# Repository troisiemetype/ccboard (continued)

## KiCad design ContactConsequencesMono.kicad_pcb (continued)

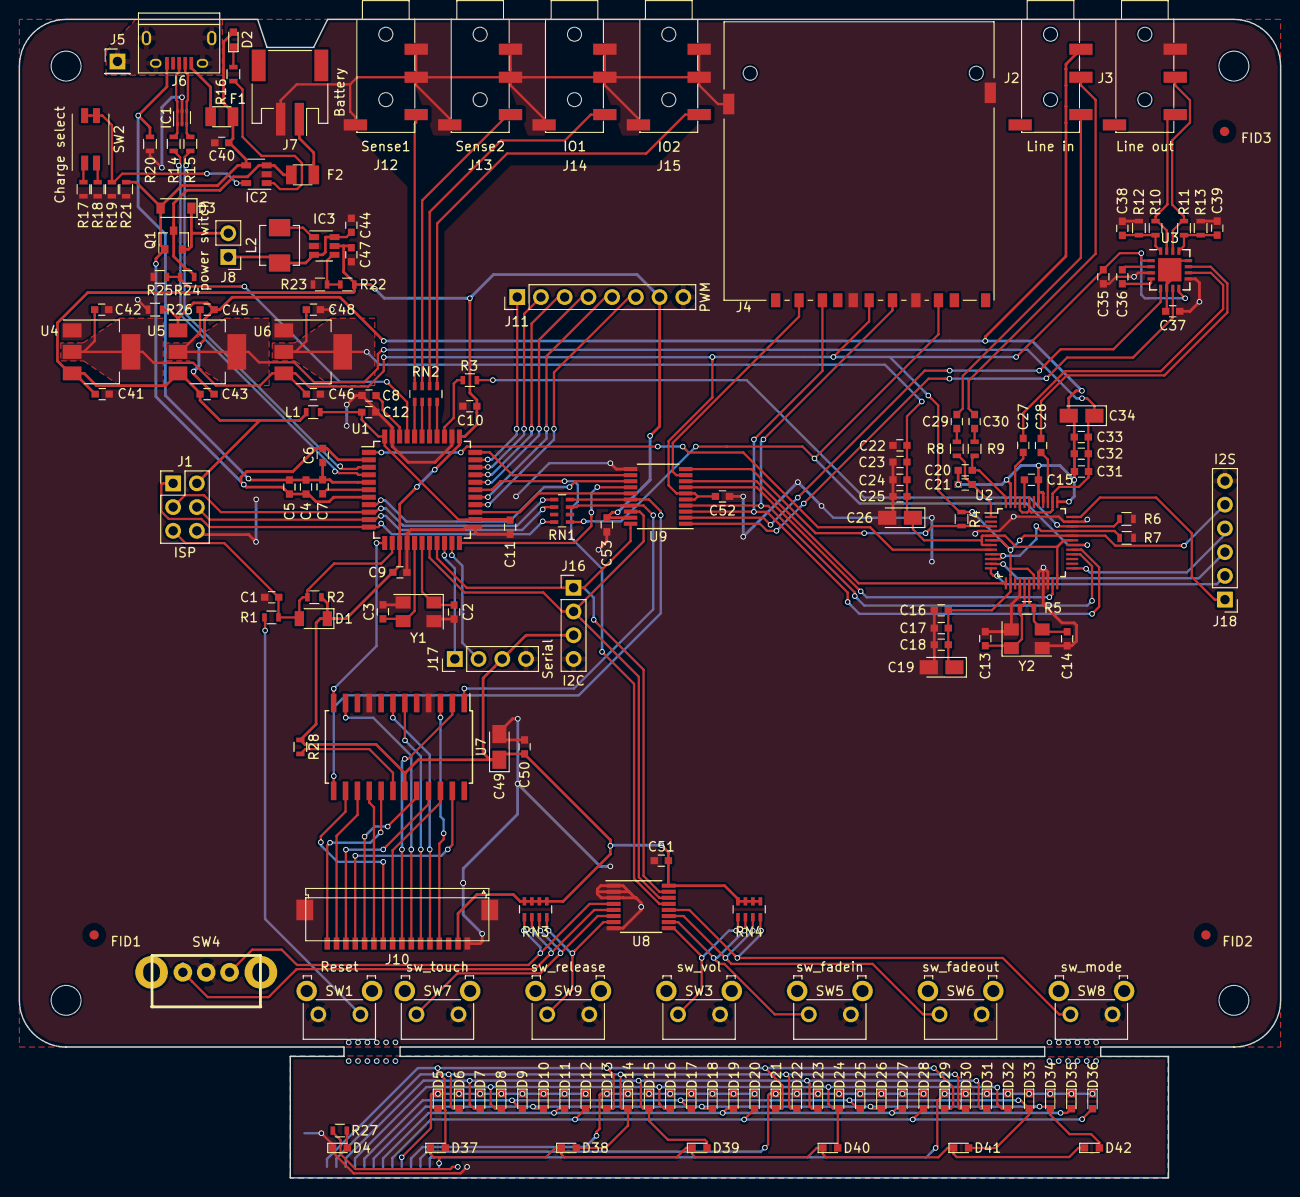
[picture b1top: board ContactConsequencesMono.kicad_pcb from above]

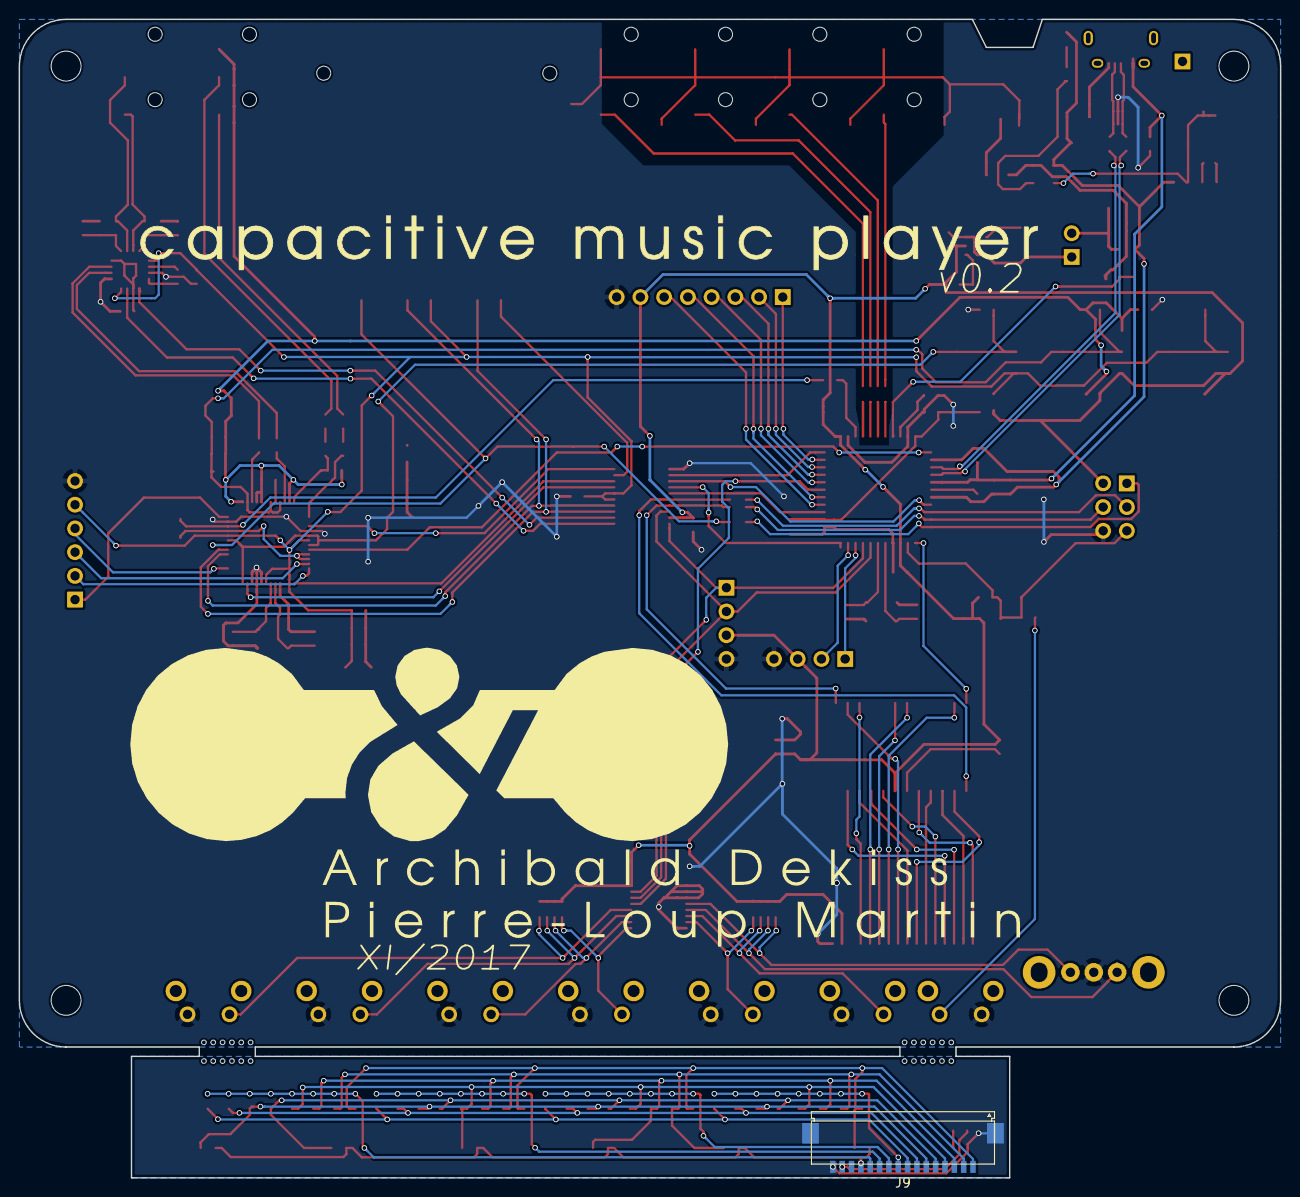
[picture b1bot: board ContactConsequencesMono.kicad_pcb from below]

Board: 2 copper layers, 135.0 x 124.0 mm, 187 parts (4 on the bottom side), 122 nets.

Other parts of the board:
svg2mod: G***; cc_Silk_60mm
svg2mod#2: G***; cc_noms
svg2mod#3: G***; cc_capacitivemusicplayer

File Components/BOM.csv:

Designator;value;Footprint;Pins;Quantity;Supplier;ref
C1,C5,C8,C9,C10,C11,C12,C15,C16,C17,C18,C22,C23,C24,C25,C31,C32,C33,C38,C39,C41,C43,C50,C51,C52,C53,C6,C47;100n;C_0603;2;28;;
C13,C14;33p;C_0603;2;2;;
C19,C26,C34,C49;10u±;CP_Tantalum_Case-A_EIA-3216-18_Reflow;2;4;Kemet;"T491A106K006AT or 
T491A106M006AT"
C2,C3;22p;C_0603;2;2;;
C20,C21,C42,C45,C48;10n;C_0603;2;5;;
C27,C28;470n;C_0603;2;2;;
C4,C46;10u;C_0603;2;2;;
C40,C44;4,7u;C_0603;2;2;;
C7,C29,C30,C35,C36,C37;1u;C_0603;2;6;;
D1;D;D_1206;2;1;;
D2,D5,D6,D7,D8,D9,D10,D11,D12,D13,D14,D15,D16,D17,D18,D19,D20,D21,D22,D23,D24,D25,D26,D27,D28,D29,D30,D31,D32,D33,D34,D35,D36;red;LED_0603;2;33;;
D4,D37,D38,D39,D40,D41,D42;green;LED_0603;2;7;;
D3;D_Schottky;D_SOD-123;2;1;;
F1;500mA;Fuse_SMD1206_Reflow;2;1;Bourns;MF-NSMF050
F2;1A;Fuse_SMD1206_Reflow;2;1;Bourns;MF-NSMF110
IC1;TPD2E1B06;SOT-5X3;6;1;Texas Instruments;TPD2E1B06
IC2,IC6;TPS73633;SOT-23-5;5;2;Texas Instruments;TPS73633MDBV
IC3;MCP73831/2-OT;SOT-23-5;5;1;Texas Instruments;"CMP73831-2ACI/OT or
CMP73831T-2ACI/OT (tape and reel)"
IC4;TPS73618;SOT-23-5;5;1;Texas Instruments;TPS73618MDBV
IC5;MCP1640-SOT;SOT-23-6;6;1;Texas Instruments;MCP1640T-I/MC
J2,J3,J11,J12,J13,J14;/;PJ320D_3.5mm_Jack;4;6;;
J4;SD_Card;SD_Card_Receptacle;13;1;MPSI;Connex SD, 9 way, push-pull, metal shield, PCB R/A SMT, UL94V-0
J6;USB_OTG;USB_Micro-B;7;1;;
J7;Battery;JST_PH_S2B-PH-SM4-TB_02x2.00mm_Angled;4;1;JST;S2B-PH-SM4-(xx-)TB
J8,J9;/;Hirose_FH12-16S-1_SH;18;2;Hirose (HRS);FH12-16S-1_SH
L1;300;L_0603;2;1;Bourns;MH1608-300Y
L2;4,7u;L_Vishay_IHLP-1616;2;1;Vishay;IFLS1616AEER100M
Q1;Q_PMOS_GSD;SOT-23;3;1;Fairchild;FDN340P
R1;330;R_0603;2;1;;
R10,R11;47k;R_0603;2;2;;
R12,R13;22k;R_0603;2;2;;
R14,R15;22;R_0603;2;2;;
R17;2,2k;R_0603;2;1;;
R18,R19;20k;R_0603;2;2;;
R2,R6,R21;10k;R_0603;2;3;;
R20,R26;0;R_0603;2;2;;
R22;750;R_0603;2;1;;
R23;240;R_0603;2;1;;
R27;1k;R_0603;2;1;;
R28;24K;R_0603;2;1;;
R3;5k;R_0603;2;1;;
R4,R7,R24,R25;100k;R_0603;2;4;;
R5;1M;R_0603;2;1;;
R8,R9,R16;470;R_0603;2;3;;
RN1;500;R_Array_Concave_4x0603;8;1;;
RN2;1k;R_Array_Concave_4x0603;8;1;;
RN3,RN4;10k;R_Array_Concave_4x0603;8;2;;
SW2;Charge select;SW_DIP_x2_W5.08mm_Slide_Copal_CHS-A;4;1;;CHS-02TB1
U1;ATMEGA32U4-AU;TQFP-44_10x10mm_Pitch0.8mm;44;1;Atmel;ATmega32U4-AU
U2;vs1053b;LQFP-48_7x7mm_Pitch0.5mm;48;1;VLSI;V1053B-L
U3;MAX9723-TQFN;QFN-16-1EP_4x4mm_Pitch0.65mm;16;1;Maxim;"MAX9723CETE or
MAX9723DETE"
U4;MAX7219;SOIC-24W_7.5x15.4mm_Pitch1.27mm;24;1;Maxim;MAX7219CWG
U5;TCA9534;TSSOP-16_4.4x5mm_Pitch0.65mm;16;1;Texas Instruments;TCA9534PWR
U6;TXS0108EPWR;TSSOP-20_4.4x6.5mm_Pitch0.65mm;20;1;Texas Instruments;TWS0108EPWR
Y1;16MHz;Crystal_SMD_5032-4pin_5.0x3.2mm;4;1;Abracon;ABM3B-16.000MHz-B2
Y2;12,288MHz;Crystal_SMD_5032-4pin_5.0x3.2mm;4;1;Abracon;ABM3B-12.288MHz-B2
;;;;;;
/;/;Total;346;158;;

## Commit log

2017-09-26 Initial commit.
2017-09-27 Board should be ok. Bargraph leds yet to do.
2017-09-28 Seems to be good for fabrication launch. Probably minor things to fix.
2017-11-01 Board modified after ckecking. Ready for fab, just need to create gerber, position and components files.
2017-11-02 v0.1 ok for fab. Quote asked to PCB maker.
2017-11-03 Updated project with connector for main power switch. Modified fabrication files.
2017-11-15 v0.2 ready for fabrication. Voltage regulators replaced by cheaper ones.
